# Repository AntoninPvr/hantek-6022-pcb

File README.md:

# Hantek 6022BE AC mod

Simple pcb to add AC coupling to the Hantek 6022BE oscilloscope. Based on the widespread mod available here: https://github.com/OpenHantek/OpenHantek6022/blob/main/docs/HANTEK6022_AC_Modification.pdf

Compatible with the [OpenHantek6022 project](https://github.com/OpenHantek/OpenHantek6022)

## Circuit

When `AC_A` is high `C1` is short so the signal is DC coupled. When `AC_A` is low `C1` is open so the signal is AC coupled.

## PCB

Back layer can be avoided especially in case of pcb milling.

## BOM
Reference | Value | Datasheet | Footprint | Qty
--- | --- | --- | --- | ---
C1,C2 | 100n | ~ | Capacitor_SMD:C_0805_2012Metric | 2
R1,R2,R3,R4 | 220 | ~ | Resistor_SMD:R_0805_2012Metric | 4
U1,U2 | TLP175A | [Datasheet](https://toshiba.semicon-storage.com/info/docget.jsp?did=13665&prodName=TLP175A) | Package_SO:MFSOP6-4_4.4x3.6mm_P1.27mm | 2

## Mounting

The pcb can be mounted on an unpopulated shield hole

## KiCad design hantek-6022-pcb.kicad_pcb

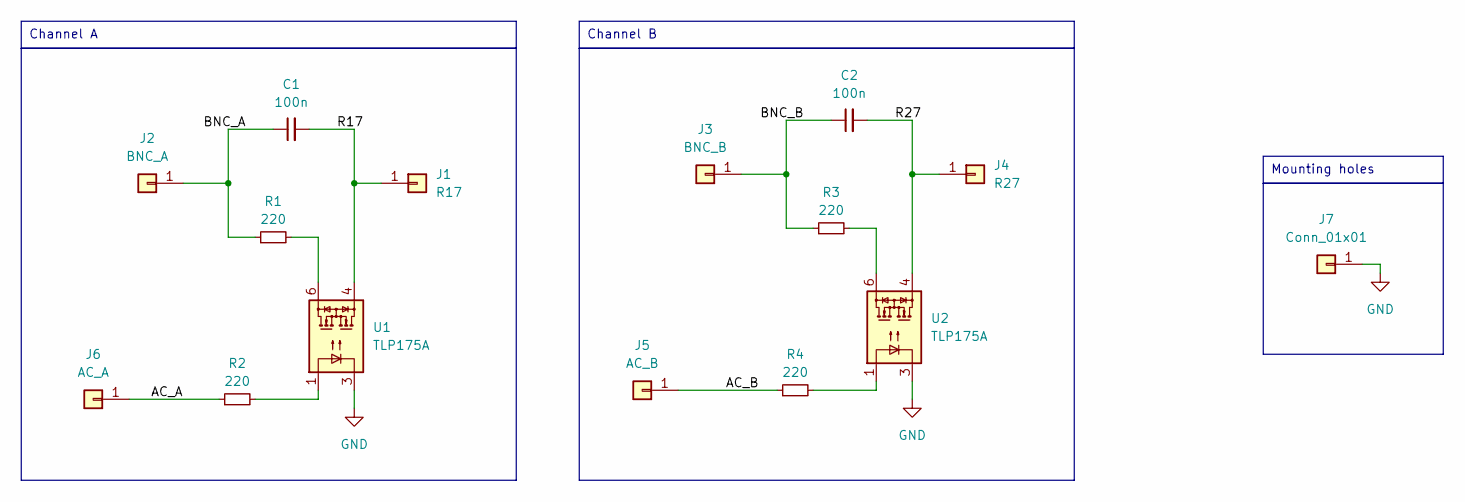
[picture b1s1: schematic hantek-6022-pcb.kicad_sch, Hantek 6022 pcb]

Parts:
C1, C2: 100n; C_0805_2012Metric
J1: R17; Pin_D1.0mm_L10.0mm
J2: BNC_A; Pin_D1.0mm_L10.0mm
J3: BNC_B; Pin_D1.0mm_L10.0mm
J4: R27; Pin_D1.0mm_L10.0mm
J5: AC_B; Pin_D1.0mm_L10.0mm
J6: AC_A; Pin_D1.0mm_L10.0mm
J7: Conn_01x01; PinHeader_1x01_P2.54mm_Vertical
R1, R2, R3, R4: 220; R_0805_2012Metric
U1, U2: TLP175A; MFSOP6-4_4.4x3.6mm_P1.27mm

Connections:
/AC_A: J6.1, R2.1
/AC_B: J5.1, R4.1
/BNC_A: C1.1, J2.1, R1.1
/BNC_B: C2.1, J3.1, R3.1
/R17: C1.2, J1.1, U1.4
/R27: C2.2, J4.1, U2.4
GND: J7.1, U1.3, U2.3
unnamed: R1.2, U1.6
unnamed: R2.2, U1.1
unnamed: R3.2, U2.6
unnamed: R4.2, U2.1

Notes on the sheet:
Mounting holes
Channel B
Channel A

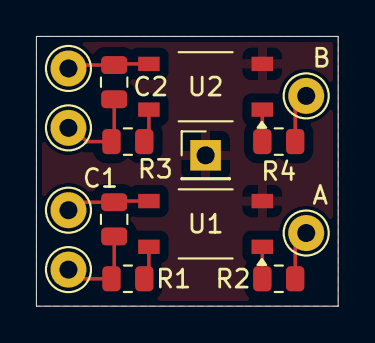
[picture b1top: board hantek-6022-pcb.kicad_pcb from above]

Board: 2 copper layers, 16.8 x 15.0 mm, 15 parts (0 on the bottom side), 11 nets.

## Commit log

2024-07-18 update gitignore
2024-07-18 reduce pcb size, add readme
